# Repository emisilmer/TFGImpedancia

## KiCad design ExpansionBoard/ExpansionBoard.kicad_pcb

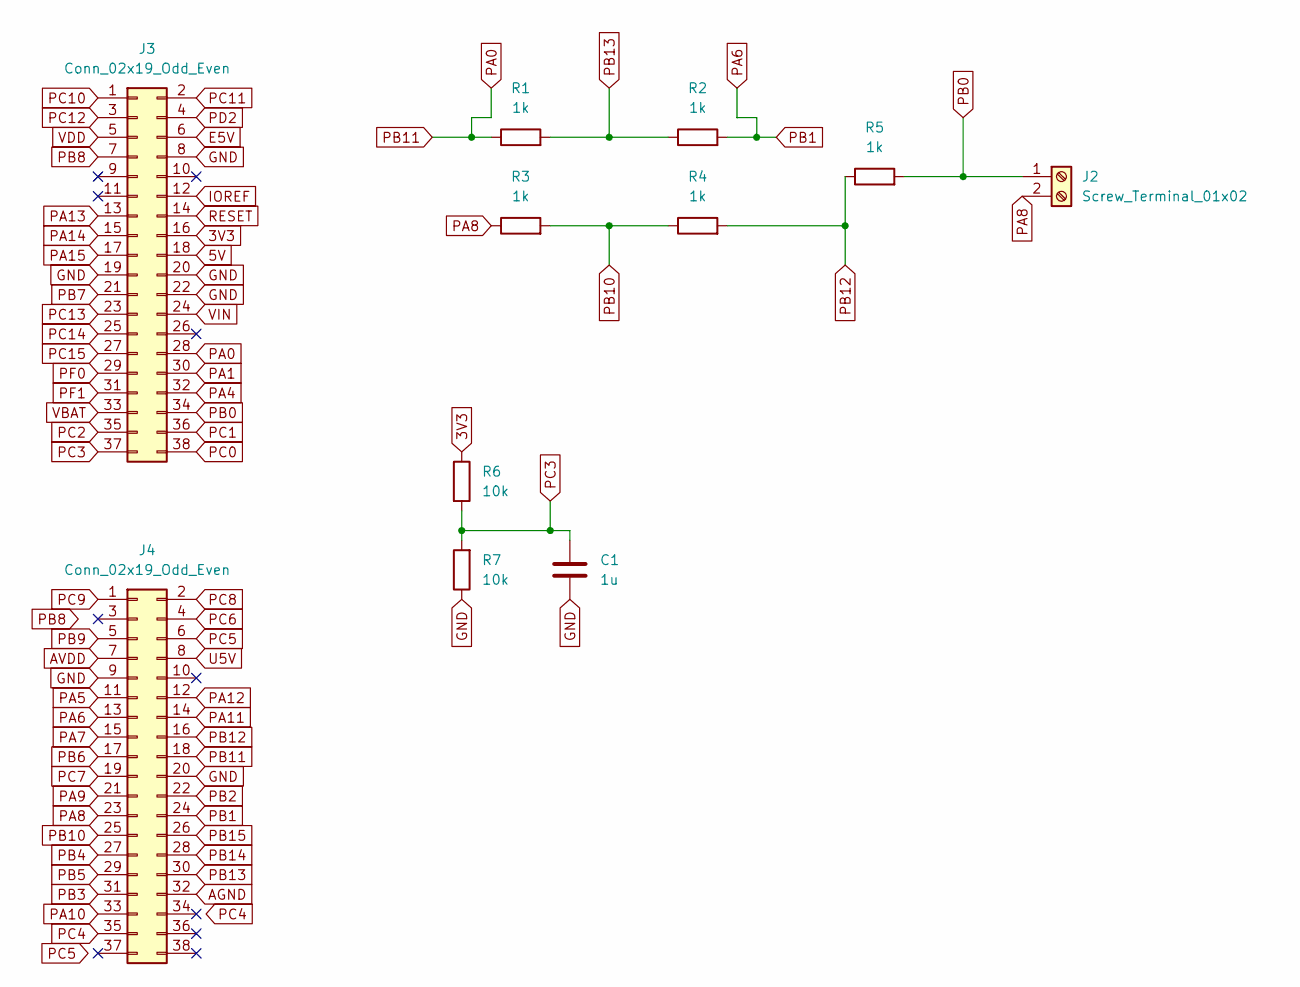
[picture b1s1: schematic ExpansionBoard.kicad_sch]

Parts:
C1: 1u; C_1206_3216Metric
J2: Screw_Terminal_01x02; TerminalBlock_Phoenix_MKDS-1,5-2-5.08_1x02_P5.08mm_Horizont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
J3, J4: Conn_02x19_Odd_Even; PinHeader_2x19_P2.54mm_Vertical
R1, R2, R3, R4, R5: 1k; R_1206_3216Metric
R6, R7: 10k; R_1206_3216Metric

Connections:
3V3: J3.16, R6.1
5V: J3.18
AGND: J4.32
AVDD: J4.7
E5V: J3.6
GND: C1.2, J3.8, J3.19, J3.20, J3.22, J4.9, J4.20, R7.1
IOREF: J3.12
PA0: J3.28, J4.18, R1.1
PA1: J3.30
PA4: J3.32
PA5: J4.11
PA6: J4.13, J4.24, R2.2
PA7: J4.15
PA8: J2.2, J4.23, R3.1
PA9: J4.21
PA10: J4.33
PA11: J4.14
PA12: J4.12
PA13: J3.13
PA14: J3.15
PA15: J3.17
PB0: J2.1, J3.34, R5.2
PB2: J4.22
PB3: J4.31
PB4: J4.27
PB5: J4.29
PB6: J4.17
PB7: J3.21
PB8: J3.7
PB9: J4.5
PB10: J4.25, R3.2, R4.1
PB12: J4.16, R4.2, R5.1
PB13: J4.30, R1.2, R2.1
PB14: J4.28
PB15: J4.26
PC0: J3.38
PC1: J3.36
PC2: J3.35
PC3: C1.1, J3.37, R6.2, R7.2
PC4: J4.35
PC5: J4.6
PC6: J4.4
PC7: J4.19
PC8: J4.2
PC9: J4.1
PC10: J3.1
PC11: J3.2
PC12: J3.3
PC13: J3.23
PC14: J3.25
PC15: J3.27
PD2: J3.4
PF0: J3.29
PF1: J3.31
RESET: J3.14
U5V: J4.8
VBAT: J3.33
VDD: J3.5
VIN: J3.24

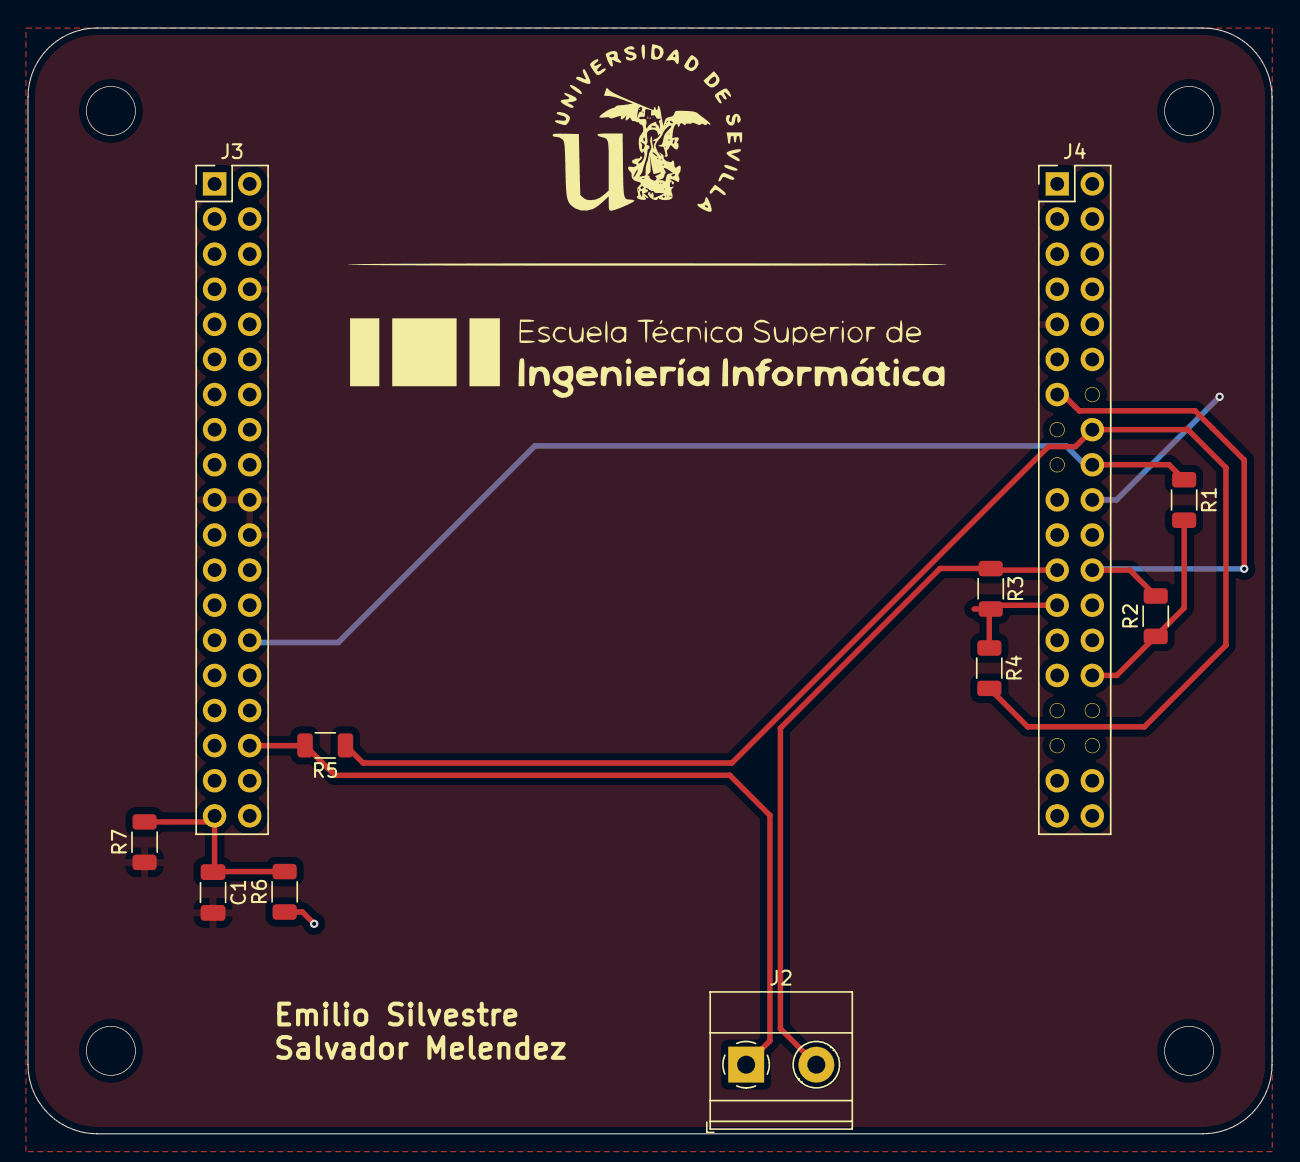
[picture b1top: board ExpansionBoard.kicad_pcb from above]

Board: 2 copper layers, 90.0 x 80.0 mm, 11 parts (0 on the bottom side), 10 nets.

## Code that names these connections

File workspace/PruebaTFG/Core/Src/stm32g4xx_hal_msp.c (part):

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
    __HAL_RCC_GPIOA_CLK_ENABLE();
    /**ADC1 GPIO Configuration
    PA0     ------> ADC1_IN1
    */
    GPIO_InitStruct.Pin = GPIO_PIN_0;
    GPIO_InitStruct.Mode = GPIO_MODE_ANALOG;
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
    __HAL_RCC_GPIOA_CLK_ENABLE();
    /**ADC2 GPIO Configuration
    PA6     ------> ADC2_IN3
    */
    GPIO_InitStruct.Pin = GPIO_PIN_6;
    GPIO_InitStruct.Mode = GPIO_MODE_ANALOG;
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    }

    /**ADC1 GPIO Configuration
    PA0     ------> ADC1_IN1
    */
    HAL_GPIO_DeInit(GPIOA, GPIO_PIN_0);

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    }

    /**ADC2 GPIO Configuration
    PA6     ------> ADC2_IN3
    */
    HAL_GPIO_DeInit(GPIOA, GPIO_PIN_6);

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
    __HAL_RCC_GPIOB_CLK_ENABLE();
    /**OPAMP3 GPIO Configuration
    PB0     ------> OPAMP3_VINP
    PB1     ------> OPAMP3_VOUT
    */
    GPIO_InitStruct.Pin = GPIO_PIN_0|GPIO_PIN_1;
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
    __HAL_RCC_GPIOB_CLK_ENABLE();
    /**OPAMP4 GPIO Configuration
    PB10     ------> OPAMP4_VINM
    PB12     ------> OPAMP4_VOUT
    PB13     ------> OPAMP4_VINP
    */
    GPIO_InitStruct.Pin = GPIO_PIN_10|GPIO_PIN_12|GPIO_PIN_13;
    GPIO_InitStruct.Mode = GPIO_MODE_ANALOG;
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    __HAL_RCC_GPIOC_CLK_ENABLE();
    __HAL_RCC_GPIOA_CLK_ENABLE();
    /**OPAMP5 GPIO Configuration
    PC3     ------> OPAMP5_VINP
    PA8     ------> OPAMP5_VOUT
    */
    GPIO_InitStruct.Pin = GPIO_PIN_3;
    GPIO_InitStruct.Mode = GPIO_MODE_ANALOG;
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  /* USER CODE END OPAMP3_MspDeInit 0 */

    /**OPAMP3 GPIO Configuration
    PB0     ------> OPAMP3_VINP
    PB1     ------> OPAMP3_VOUT
    */
    HAL_GPIO_DeInit(GPIOB, GPIO_PIN_0|GPIO_PIN_1);
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  /* USER CODE END OPAMP4_MspDeInit 0 */

    /**OPAMP4 GPIO Configuration
    PB10     ------> OPAMP4_VINM
    PB12     ------> OPAMP4_VOUT
    PB13     ------> OPAMP4_VINP
    */
    HAL_GPIO_DeInit(GPIOB, GPIO_PIN_10|GPIO_PIN_12|GPIO_PIN_13);

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  /* USER CODE END OPAMP5_MspDeInit 0 */

    /**OPAMP5 GPIO Configuration
    PC3     ------> OPAMP5_VINP
    PA8     ------> OPAMP5_VOUT
    */
    HAL_GPIO_DeInit(GPIOC, GPIO_PIN_3);

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
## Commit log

2023-10-09 prueba github
2023-10-09 PruebaSalva
2023-10-19 Añadido Workspace CubeIde de prueba
2023-10-19 Borrado ficheros de prueba
2023-10-19 Avance en el proyecto, fallo en lectura DAC valores negativos y flotantes
2023-10-30 Arreglado DAC para generar señal senoidal con valores positivos sin signo
2023-10-31 Intento de generar señal del DAC usando interrupciones DMA (No funciona)
2023-11-09 Fallos en el dac
2023-11-13 Fallos en el DMA del DAC
2023-11-27 Funciona DAC y Opams con DMA
2023-11-27 No para punto ruptura ADC configurado
2023-11-30 LED Blink
2023-12-01 Impletacion OPAMs Externos
2023-12-18 CalculaLut funciona, AjustaTimers no
2024-01-15 Ajusta Timers terminado sin comprobar
2024-01-15 Borrado .project residual
2024-01-31 Funciones terminadas sin funcionar
2024-01-31 Revisado ajusta timers por terminar
2024-04-08 Ajusta Timer Configurado Correctamente
2024-04-08 Implementado OPAM5 para correccion tierra virtual
2024-05-29 Añadida PCB no ADCs
2024-06-02 Añadido y configurados 2 ADC en diferential
2024-06-03 Revision PCB y ADCs
2024-06-04 Revision PCB e Intento ADCs
2024-06-10 Add UART configuration.
2024-06-10 no message
2024-06-10 Resto del código para el printf
2024-06-12 Configurado ADC2
2024-06-22 TFG Finalizado V1

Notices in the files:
workspace/PruebaTFG/Core/Src/stm32g4xx_hal_msp.c:
Copyright (c) 2023 STMicroelectronics.
All rights reserved.
This software is licensed under terms that can be found in the LICENSE file
